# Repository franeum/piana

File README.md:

# piana

## bill of materials (BOM)

- [pro micro]()
- [rwcl-0516]()
- [dfplayer mini]()
- pcb rwcl-p516
- pcb dfplayer promicro
- speaker
- 2 audio jack (mono unbalanced) (dfplayer -> speaker)
- shielded audio cable
- [Scatola da derivazione elettrica in plastica IP65](https://www.ave.it/catalog/prodotto/sd1004/) (2) 5,52
- [cavo cat6 schermato]()

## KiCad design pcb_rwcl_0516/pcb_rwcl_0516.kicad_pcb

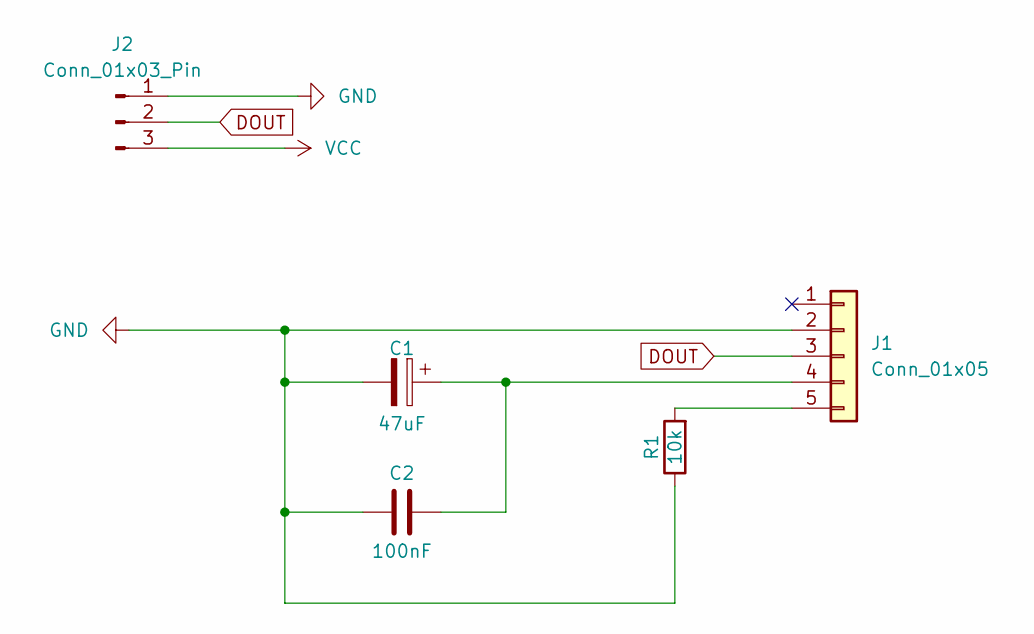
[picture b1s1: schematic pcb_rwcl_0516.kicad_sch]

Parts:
C1: 47uF; CP_Radial_D6.3mm_P2.50mm
C2: 100nF; C_Disc_D5.0mm_W2.5mm_P5.00mm
J1: Conn_01x05; PinHeader_1x05_P2.54mm_Vertical
J2: Conn_01x03_Pin; TerminalBlock_bornier-3_P5.08mm
R1: 10k; R_Axial_DIN0207_L6.3mm_D2.5mm_P7.62mm_Horizontal

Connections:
DOUT: J1.3, J2.2
GND: C1.2, C2.2, J1.2, J2.1, R1.1
unnamed: C1.1, C2.1, J1.4
unnamed: J1.5, R1.2
VCC: J2.3

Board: 2 copper layers, 7 parts (0 on the bottom side), 4 nets, no tracks yet.

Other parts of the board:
HOLE1, HOLE2: MountingHole_3.2mm_M3
